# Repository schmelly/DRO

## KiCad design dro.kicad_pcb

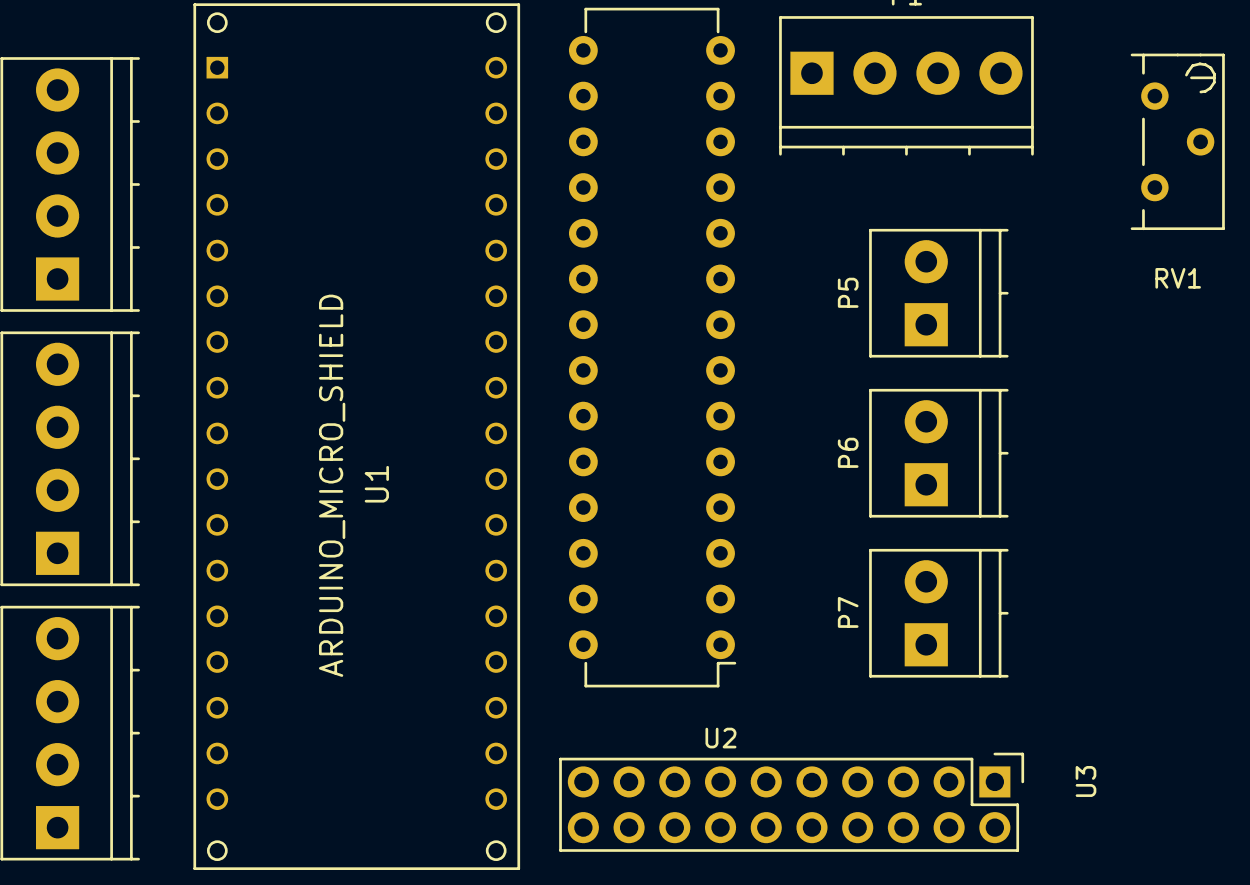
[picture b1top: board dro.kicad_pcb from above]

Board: 2 copper layers, 11 parts (0 on the bottom side), 31 nets.

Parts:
P1: POWER; TerminalBlock_Pheonix_PT-3.5mm_4pol
P2: X_SENSOR; TerminalBlock_Pheonix_PT-3.5mm_4pol
P3: Y_SENSOR; TerminalBlock_Pheonix_PT-3.5mm_4pol
P4: Z_SENSOR; TerminalBlock_Pheonix_PT-3.5mm_4pol
P5: SX; TerminalBlock_Pheonix_PT-3.5mm_2pol
P6: SY; TerminalBlock_Pheonix_PT-3.5mm_2pol
P7: SZ; TerminalBlock_Pheonix_PT-3.5mm_2pol
RV1: 10K; Potentiometer_Bourns_3296Y_3-8Zoll_Angular_ScrewUp
U1: ARDUINO_MICRO_SHIELD
U2: MCP23S17; DIP-28_W7.62mm
U3: TLX-1013-E0; Pin_Header_Straight_2x10

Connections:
+5V: P1.1, P2.1, P3.1, P4.1, P5.2, P6.2, P7.2, U2.9
+12V: P1.2, U1.VI
-8V: RV1.2, U3.3, U3.4
-12V: P1.3, RV1.1
GND: P1.4, P2.2, P3.2, P4.2, U2.10, U3.2, U3.19
unnamed: P2.3, U1.3
unnamed: P2.4, U1.2
unnamed: P3.3, U1.5
unnamed: P3.4, U1.4
unnamed: P4.3, U1.7
unnamed: P4.4, U1.6
unnamed: P5.1, U2.8
unnamed: P6.1, U2.7
unnamed: P7.1, U2.6
unnamed: U1.MI, U2.14
unnamed: U1.MO, U2.13
unnamed: U1.SCK, U2.12
unnamed: U1.SS, U2.11
unnamed: U2.1, U3.7
unnamed: U2.2, U3.5
unnamed: U2.3, U3.6
unnamed: U2.4, U3.8
unnamed: U2.5, U3.10
unnamed: U2.21, U3.12
unnamed: U2.22, U3.14
unnamed: U2.23, U3.16
unnamed: U2.24, U3.18
unnamed: U2.25, U3.17
unnamed: U2.26, U3.15
unnamed: U2.27, U3.13
unnamed: U2.28, U3.11

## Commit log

2016-11-20 current state
2016-11-28 Added schematic and pcb for as5311 sensor board
2017-01-18 progress on the dro web app
2017-02-04 - More progress on the DRO WebApp - Repository cleanup - Added GPL (for webapp) and CC-BY-SA-4.0 (pcb design) licences
2017-02-04 Added first test release
2017-02-05 Added component to store and manage configuration data. Upgraded angular to 2.4.6.
2017-02-06 added server-side configuration saving/loading
2017-02-06 more work on visuals (icons, layout)
2017-02-08 Started working on a helper for pocket milling
2017-02-09 Started working on a component for managing user defined coordinates
2017-02-12 more progress on the pocket helper; added button to enable fullscreen mode
2017-02-13 Progress on user coordinate handling
2017-02-15 updated release for current development snapshot
2017-02-21 Added helper function for contour milling; smaller fixes and a bit of code cleanup
2017-02-21 Added release including contour function
2017-02-23 Implemented readings from z-axis; implemented RPi shutdown/reboot from webapp
2017-05-04 Updated dependencies to angular 4.1.0; Adapted layout to fit 4:3 screens
2017-11-15 migration to angular 5.0 and code cleanup
2017-11-15 fixed setting of axis absolut position when inverted
